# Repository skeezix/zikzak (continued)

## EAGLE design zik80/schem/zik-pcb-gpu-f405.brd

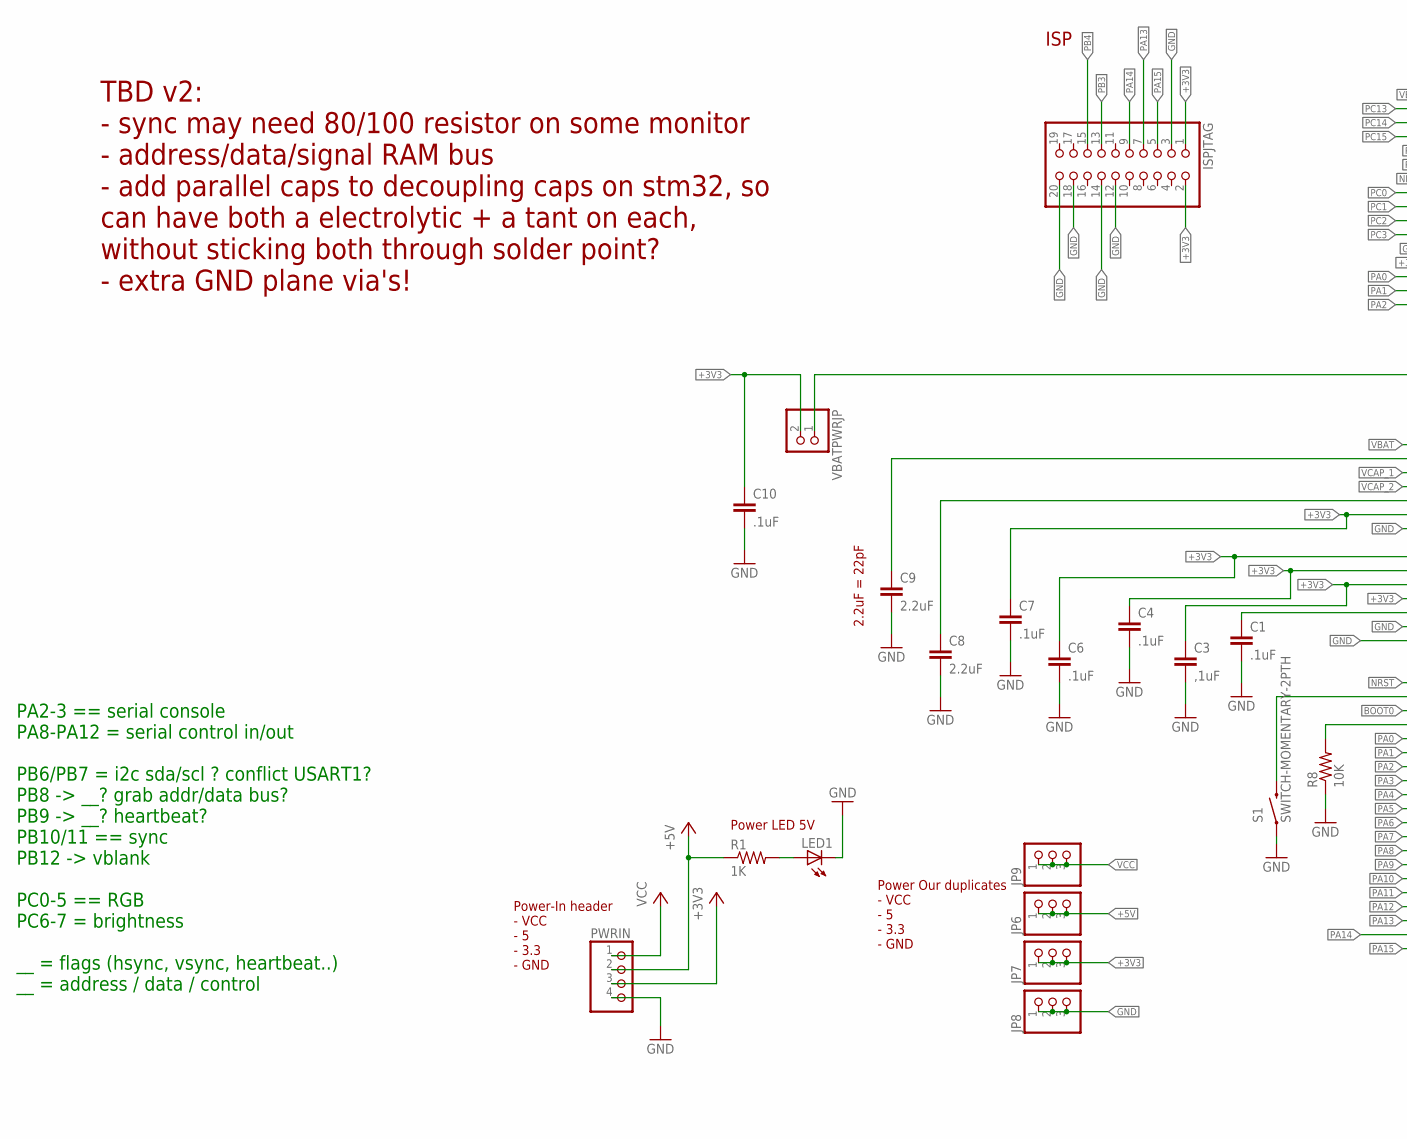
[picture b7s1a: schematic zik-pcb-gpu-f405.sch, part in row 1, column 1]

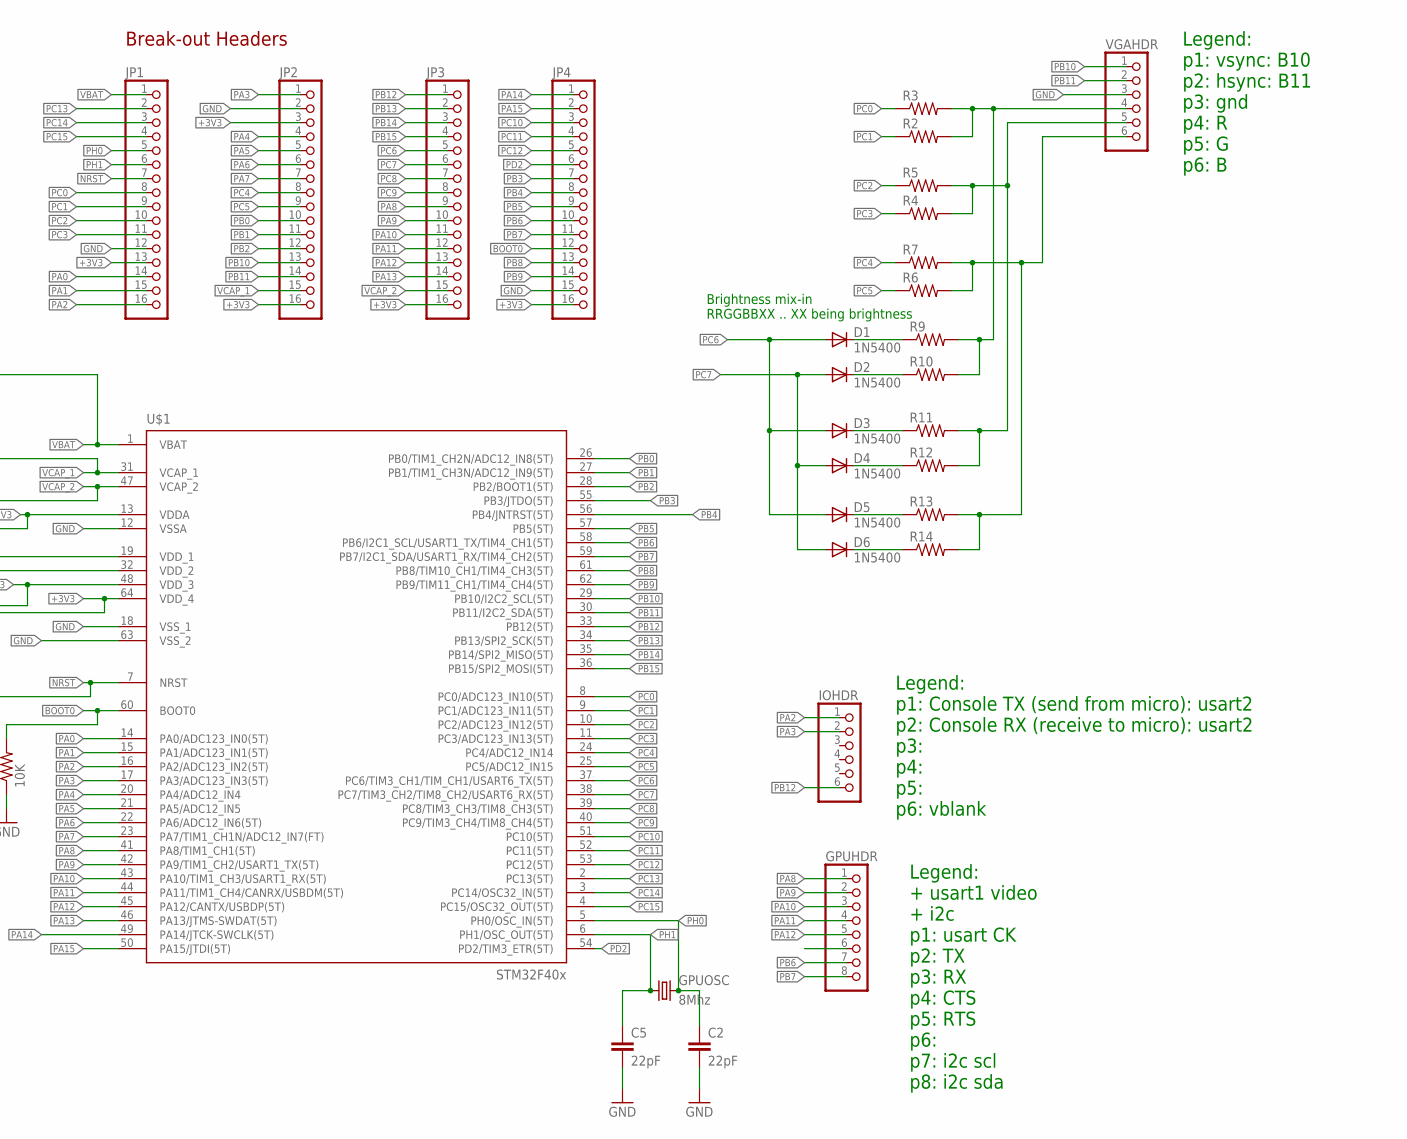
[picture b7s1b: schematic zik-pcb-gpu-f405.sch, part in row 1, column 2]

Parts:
C1, C4, C6, C7, C10: .1uF; C025-025X050
C2, C5: 22pF; C025-025X050
C3: ,1uF; C025-025X050
C8, C9: 2.2uF; C025-025X050
D1, D2, D3, D4, D5, D6: 1N5400; DO201-15
GPUHDR: PINHD-1X8; 1X08
GPUOSC: 8Mhz; HC49US
IOHDR: PINHD-1X6; 1X06
ISPJTAG: PINHD-2X10; 2X10
JP1, JP2, JP3, JP4: PINHD-1X16; 1X16
JP6, JP7, JP8, JP9: PINHD-1X3; 1X03
LED1: LED5MM
PWRIN: PINHD-1X4; 1X04
R1: 1K; 0207/10
R2, R3, R4, R5, R6, R7, R9, R10, R11, R12, R13, R14: R-US_0207/10; 0207/10
R8: 10K; 0207/10
S1: SWITCH-MOMENTARY-2PTH; TACTILE-PTH
U$1: STM32F405R; TQFP64
VBATPWRJP: PINHD-1X2; 1X02
VGAHDR: PINHD-1X6; 1X06

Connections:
+3V3: C1.1, C3.1, C4.1, C6.1, C7.1, C10.1, ISPJTAG.1, ISPJTAG.2, JP1.13, JP2.3, JP2.16, JP3.16, JP4.16, JP7.1, JP7.2, JP7.3, PWRIN.3, U$1.13 (VDDA), U$1.19 (VDD_1), U$1.32 (VDD_2), U$1.48 (VDD_3), U$1.64 (VDD_4), VBATPWRJP.2
+5V: JP6.1, JP6.2, JP6.3, PWRIN.2, R1.1
BOOT0: JP4.12, R8.2, U$1.60 (BOOT0)
GND: C1.2, C2.2, C3.2, C4.2, C5.2, C6.2, C7.2, C8.2, C9.2, C10.2, ISPJTAG.3, ISPJTAG.12, ISPJTAG.14, ISPJTAG.18, ISPJTAG.20, JP1.12, JP2.2, JP4.15, JP8.1, JP8.2, JP8.3, LED1.K (C), PWRIN.4, R8.1, S1.1, U$1.12 (VSSA), U$1.18 (VSS_1), U$1.63 (VSS_2), VGAHDR.3
unnamed: LED1.A, R1.2
unnamed: D1.C, R9.1
unnamed: R4.2, R5.2, R11.2, R12.2, VGAHDR.5
unnamed: D2.C, R10.1
unnamed: R6.2, R7.2, R13.2, R14.2, VGAHDR.6
unnamed: R2.2, R3.2, R9.2, R10.2, VGAHDR.4
unnamed: D3.C, R11.1
unnamed: D4.C, R12.1
unnamed: D5.C, R13.1
unnamed: D6.C, R14.1
NRST: JP1.7, S1.3 (2), U$1.7 (NRST)
PA0: JP1.14, U$1.14 (PA0/ADC123_IN0(5T))
PA1: JP1.15, U$1.15 (PA1/ADC123_IN1(5T))
PA2: IOHDR.1, JP1.16, U$1.16 (PA2/ADC123_IN2(5T))
PA3: IOHDR.2, JP2.1, U$1.17 (PA3/ADC123_IN3(5T))
PA4: JP2.4, U$1.20 (PA4/ADC12_IN4)
PA5: JP2.5, U$1.21 (PA5/ADC12_IN5)
PA6: JP2.6, U$1.22 (PA6/ADC12_IN6(5T))
PA7: JP2.7, U$1.23 (PA7/TIM1_CH1N/ADC12_IN7(FT))
PA8: GPUHDR.1, JP3.9, U$1.41 (PA8/TIM1_CH1(5T))
PA9: GPUHDR.2, JP3.10, U$1.42 (PA9/TIM1_CH2/USART1_TX(5T))
PA10: GPUHDR.3, JP3.11, U$1.43 (PA10/TIM1_CH3/USART1_RX(5T))
PA11: GPUHDR.4, JP3.12, U$1.44 (PA11/TIM1_CH4/CANRX/USBDM(5T))
PA12: GPUHDR.5, JP3.13, U$1.45 (PA12/CANTX/USBDP(5T))
PA13: ISPJTAG.7, JP3.14, U$1.46 (PA13/JTMS-SWDAT(5T))
PA14: ISPJTAG.9, JP4.1, U$1.49 (PA14/JTCK-SWCLK(5T))
PA15: ISPJTAG.5, JP4.2, U$1.50 (PA15/JTDI(5T))
PB0: JP2.10, U$1.26 (PB0/TIM1_CH2N/ADC12_IN8(5T))
PB1: JP2.11, U$1.27 (PB1/TIM1_CH3N/ADC12_IN9(5T))
PB2: JP2.12, U$1.28 (PB2/BOOT1(5T))
PB3: ISPJTAG.13, JP4.7, U$1.55 (PB3/JTDO(5T))
PB4: ISPJTAG.15, JP4.8, U$1.56 (PB4/JNTRST(5T))
PB5: JP4.9, U$1.57 (PB5(5T))
PB6: GPUHDR.7, JP4.10, U$1.58 (PB6/I2C1_SCL/USART1_TX/TIM4_CH1(5T))
PB7: GPUHDR.8, JP4.11, U$1.59 (PB7/I2C1_SDA/USART1_RX/TIM4_CH2(5T))
PB8: JP4.13, U$1.61 (PB8/TIM10_CH1/TIM4_CH3(5T))
PB9: JP4.14, U$1.62 (PB9/TIM11_CH1/TIM4_CH4(5T))
PB10: JP2.13, U$1.29 (PB10/I2C2_SCL(5T)), VGAHDR.1
PB11: JP2.14, U$1.30 (PB11/I2C2_SDA(5T)), VGAHDR.2
PB12: IOHDR.6, JP3.1, U$1.33 (PB12(5T))
PB13: JP3.2, U$1.34 (PB13/SPI2_SCK(5T))
PB14: JP3.3, U$1.35 (PB14/SPI2_MISO(5T))
PB15: JP3.4, U$1.36 (PB15/SPI2_MOSI(5T))
PC0: JP1.8, R3.1, U$1.8 (PC0/ADC123_IN10(5T))
PC1: JP1.9, R2.1, U$1.9 (PC1/ADC123_IN11(5T))
PC2: JP1.10, R5.1, U$1.10 (PC2/ADC123_IN12(5T))
PC3: JP1.11, R4.1, U$1.11 (PC3/ADC123_IN13(5T))
PC4: JP2.8, R7.1, U$1.24 (PC4/ADC12_IN14)
PC5: JP2.9, R6.1, U$1.25 (PC5/ADC12_IN15)
PC6: D1.A, D3.A, D5.A, JP3.5, U$1.37 (PC6/TIM3_CH1/TIM_CH1/USART6_TX(5T))
PC7: D2.A, D4.A, D6.A, JP3.6, U$1.38 (PC7/TIM3_CH2/TIM8_CH2/USART6_RX(5T))
PC8: JP3.7, U$1.39 (PC8/TIM3_CH3/TIM8_CH3(5T))
PC9: JP3.8, U$1.40 (PC9/TIM3_CH4/TIM8_CH4(5T))
PC10: JP4.3, U$1.51 (PC10(5T))
PC11: JP4.4, U$1.52 (PC11(5T))
PC12: JP4.5, U$1.53 (PC12(5T))
PC13: JP1.2, U$1.2 (PC13(5T))
PC14: JP1.3, U$1.3 (PC14/OSC32_IN(5T))
PC15: JP1.4, U$1.4 (PC15/OSC32_OUT(5T))
PD2: JP4.6, U$1.54 (PD2/TIM3_ETR(5T))
PH0: C2.1, GPUOSC.2, JP1.5, U$1.5 (PH0/OSC_IN(5T))
PH1: C5.1, GPUOSC.1, JP1.6, U$1.6 (PH1/OSC_OUT(5T))
VBAT: JP1.1, U$1.1 (VBAT), VBATPWRJP.1
VCAP_1: C9.1, JP2.15, U$1.31 (VCAP_1)
VCAP_2: C8.1, JP3.15, U$1.47 (VCAP_2)
VCC: JP9.1, JP9.2, JP9.3, PWRIN.1

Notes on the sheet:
Power-In header - VCC - 5 - 3.3 - GND
Break-out Headers
ISP
Power Our duplicates - VCC - 5 - 3.3 - GND
2.2uF = 22pF
TBD v2: - sync may need 80/100 resistor on some monitor - address/data/signal RAM bus - add parallel caps to decoupling caps on stm32, so can have both a electrolytic + a tant on each, without sticking both through solder point? - extra GND plane via's!
Power LED 5V
Legend: p1: vsync: B10 p2: hsync: B11 p3: gnd p4: R p5: G p6: B
PA2-3 == serial console PA8-PA12 = serial control in/out PB6/PB7 = i2c sda/scl ? conflict USART1? PB8 -> __? grab addr/data bus? PB9 -> __? heartbeat? PB10/11 == sync PB12 -> vblank PC0-5 == RGB PC6-7 = brightness __ = flags (hsync, vsync, heartbeat..) __ = address / data / control
Legend: p1: Console TX (send from micro): usart2 p2: Console RX (receive to micro): usart2 p3: p4: p5: p6: vblank
Legend: + usart1 video + i2c p1: usart CK p2: TX p3: RX p4: CTS p5: RTS p6: p7: i2c scl p8: i2c sda
Brightness mix-in RRGGBBXX .. XX being brightness

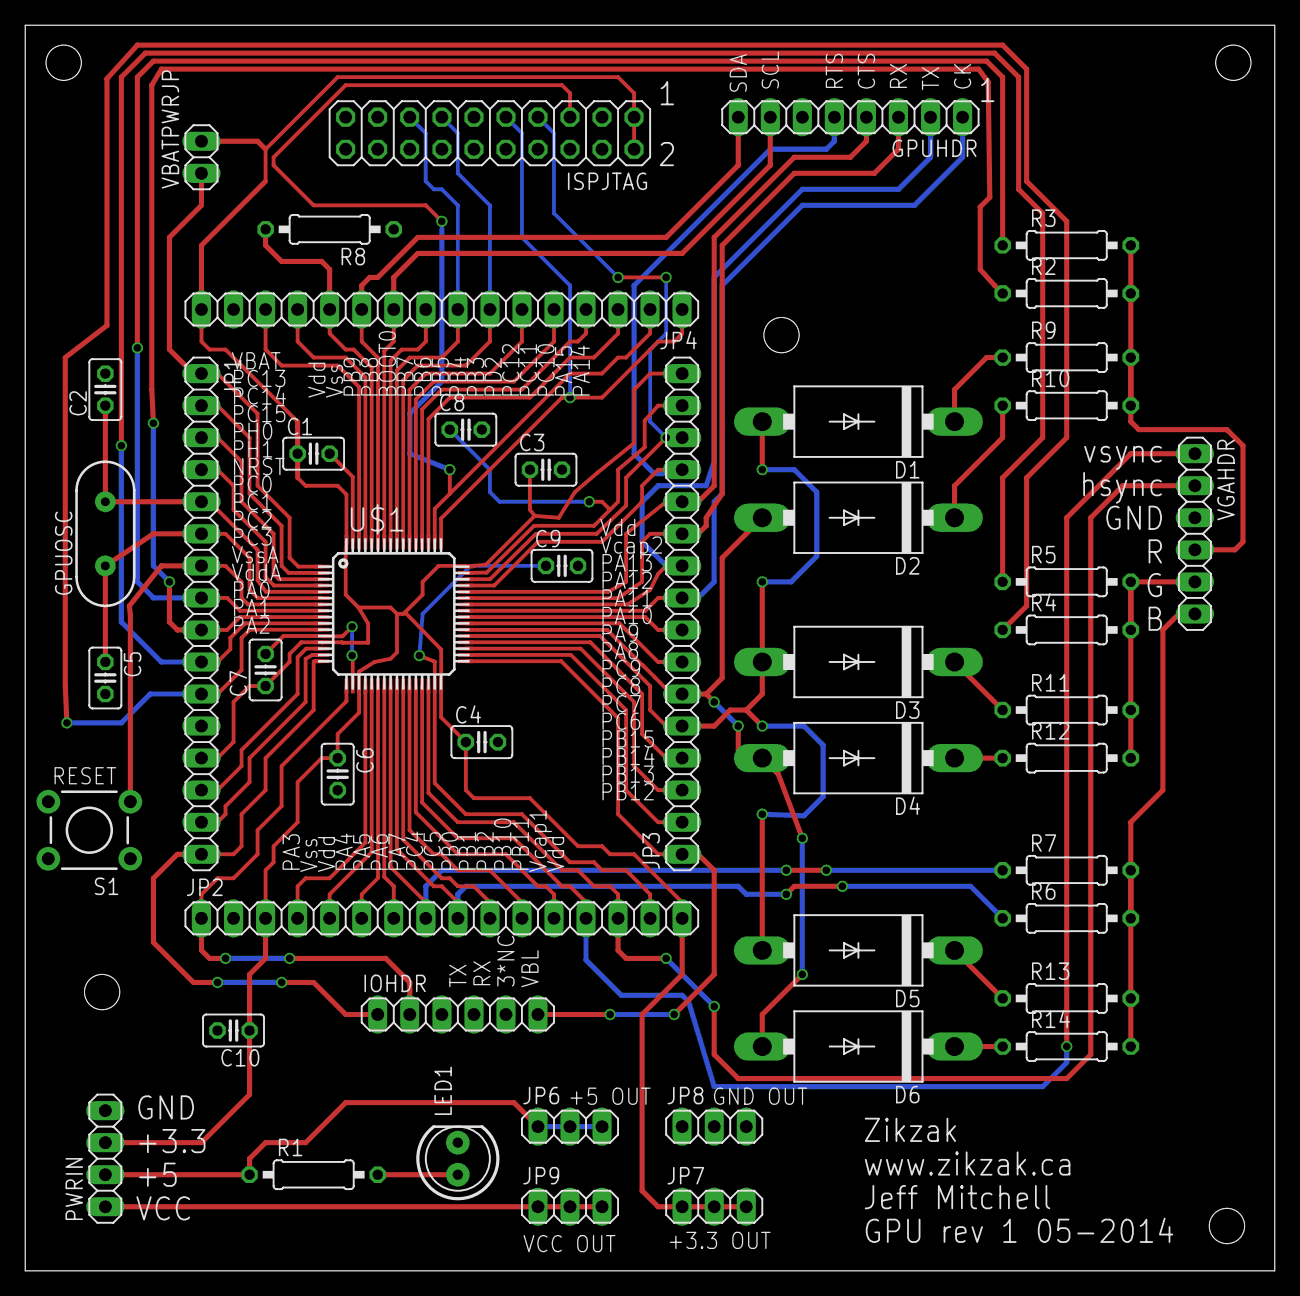
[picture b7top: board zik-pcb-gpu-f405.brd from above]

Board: 2 copper layers, 99.0 x 98.7 mm, 48 parts (0 on the bottom side), 70 nets.

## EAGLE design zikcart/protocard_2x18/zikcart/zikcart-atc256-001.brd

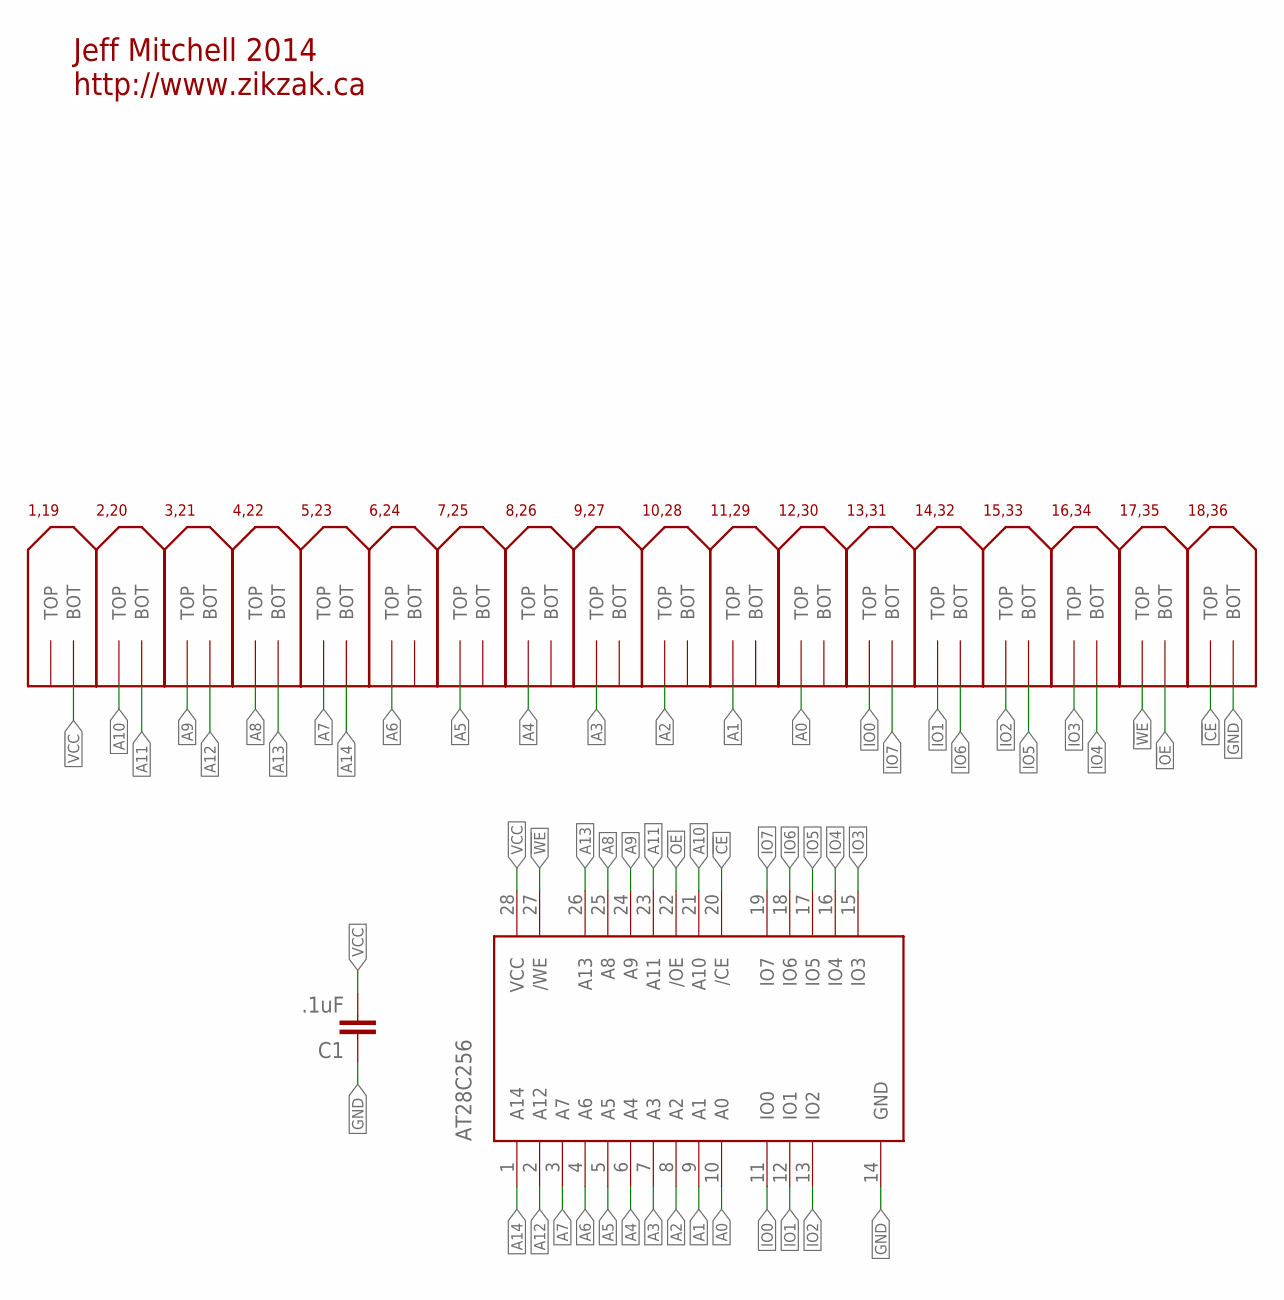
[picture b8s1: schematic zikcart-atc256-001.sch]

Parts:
1,19, 2,20, 3,21, 4,22, 5,23, 6,24, 7,25, 8,26, 9,27, 10,28, 11,29, 12,30, 13,31, 14,32, 15,33, 16,34, 17,35, 18,36: ZIKZAKFINGERPAIR2X18
AT28C256: AT28C256; DIL28-6
C1: .1uF; C025-030X050

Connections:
!CE!: 18,36.P$1 (TOP), AT28C256.20 (/CE)
!OE!: 17,35.P$2 (BOT), AT28C256.22 (/OE)
!WE!: 17,35.P$1 (TOP), AT28C256.27 (/WE)
A0: 12,30.P$1 (TOP), AT28C256.10 (A0)
A1: 11,29.P$1 (TOP), AT28C256.9 (A1)
A2: 10,28.P$1 (TOP), AT28C256.8 (A2)
A3: 9,27.P$1 (TOP), AT28C256.7 (A3)
A4: 8,26.P$1 (TOP), AT28C256.6 (A4)
A5: 7,25.P$1 (TOP), AT28C256.5 (A5)
A6: 6,24.P$1 (TOP), AT28C256.4 (A6)
A7: 5,23.P$1 (TOP), AT28C256.3 (A7)
A8: 4,22.P$1 (TOP), AT28C256.25 (A8)
A9: 3,21.P$1 (TOP), AT28C256.24 (A9)
A10: 2,20.P$1 (TOP), AT28C256.21 (A10)
A11: 2,20.P$2 (BOT), AT28C256.23 (A11)
A12: 3,21.P$2 (BOT), AT28C256.2 (A12)
A13: 4,22.P$2 (BOT), AT28C256.26 (A13)
A14: 5,23.P$2 (BOT), AT28C256.1 (A14)
GND: 18,36.P$2 (BOT), AT28C256.14 (GND), C1.1
IO0: 13,31.P$1 (TOP), AT28C256.11 (IO0)
IO1: 14,32.P$1 (TOP), AT28C256.12 (IO1)
IO2: 15,33.P$1 (TOP), AT28C256.13 (IO2)
IO3: 16,34.P$1 (TOP), AT28C256.15 (IO3)
IO4: 16,34.P$2 (BOT), AT28C256.16 (IO4)
IO5: 15,33.P$2 (BOT), AT28C256.17 (IO5)
IO6: 14,32.P$2 (BOT), AT28C256.18 (IO6)
IO7: 13,31.P$2 (BOT), AT28C256.19 (IO7)
VCC: 1,19.P$2 (BOT), AT28C256.28 (VCC), C1.2

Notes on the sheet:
Jeff Mitchell 2014 http://www.zikzak.ca

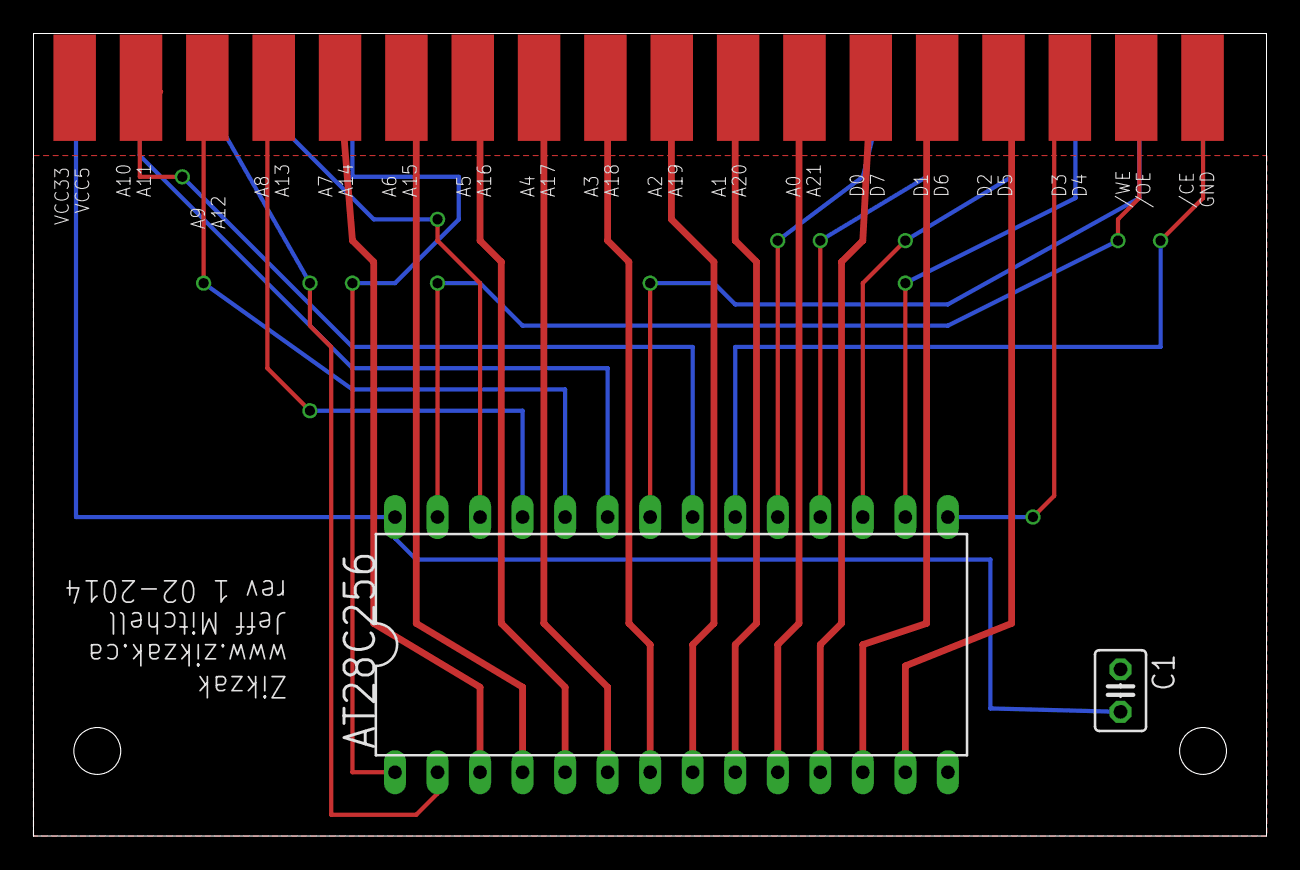
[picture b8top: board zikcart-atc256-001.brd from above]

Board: 2 copper layers, 73.6 x 47.9 mm, 20 parts (0 on the bottom side), 28 nets.

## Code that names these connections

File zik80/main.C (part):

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  OCR0B = 0;
  
  // Timer 1 - vertical sync pulses
  DDRD |= (1<<PD4); // vsync
  Timer1::setMode (15, Timer1::PRESCALE_1024, Timer1::CLEAR_B_ON_COMPARE);
  OCR1A = 259;  // 16666 / 64 uS = 260 (less one)
  OCR1B = 0;    // 64 / 64 uS = 1 (less one)
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  TIMSK1 = bit (TOIE1);  // interrupt on overflow on timer 1

  // Timer 2 - horizontal sync pulses
  DDRD |= (1<<PD6); // hsync
  Timer2::setMode (7, Timer2::PRESCALE_8, Timer2::CLEAR_B_ON_COMPARE);
  OCR2A = 63;   // 32 / 0.5 uS = 64 (less one)
  OCR2B = 7;    // 4 / 0.5 uS = 8 (less one)
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  // baud rate must be zero before enabling the transmitter
  UBRR0 = 0;  // USART Baud Rate Register
  //pinMode (MSPIM_SCK, OUTPUT);   // set XCK pin as output to enable master mode
  DDRB |= (1<<PB0);
  UCSR0B = 0; 
  UCSR0C = bit (UMSEL00) | bit (UMSEL01) | bit (UCPHA0) | bit (UCPOL0);  // Master SPI mode

  // prepare to sleep between horizontal sync pulses  
  set_sleep_mode ( SLEEP_MODE_IDLE );  

  DDRD |= (1<<PD0); // red
  DDRD |= (1<<PD1); // green
  DDRD |= (1<<PD2); // blue

  // JOY: set up pin change interupts
  EICRA &= ~ ( (1 << ISC11) | (1 << ISC10) ); // reset: clear ISC11+ISC10 (ISC1x for vect1 which we need for joy)
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}  // end of loop

volatile unsigned char _g_joy_state = 0; // so we can know which pins changed since last interupt
#define JOYMASK ( (1<<PB2) | (1<<PB3) | (1<<PB4) | (1<<PB5) | (1<<PB6) )
ISR(PCINT1_vect)
{
  unsigned char delta = _g_joy_state ^ PINB;

  if ( delta & (1<<PB2) ) {

    // CH1: edge has gone up, or down?
    if ( PINB & ( 1 << PB2 ) ) {
      // JOY UP: edge has gone high (nolonger pointing up)
      textbuf [ 0 ][ 0 ] = ' ';

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
  textbuf [ 0 ][ 4 ] = 'C';

  if ( PINC & ( 1 << PC5 ) ) {
    textbuf [ 0 ][ 2 ] = 'K';
  }

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
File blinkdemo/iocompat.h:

/*
 * ----------------------------------------------------------------------------
 * "THE BEER-WARE LICENSE" (Revision 42):
 * <joerg@FreeBSD.ORG> wrote this file.  As long as you retain this notice you
 * can do whatever you want with this stuff. If we meet some day, and you think
 * this stuff is worth it, you can buy me a beer in return.        Joerg Wunsch
 * ----------------------------------------------------------------------------
 *
 * IO feature compatibility definitions for various AVRs.
 *
 * $Id: iocompat.h 1638 2008-03-17 21:52:00Z joerg_wunsch $
 */

#if !defined(IOCOMPAT_H)
#define IOCOMPAT_H 1

/*
 * Device-specific adjustments:
 *
 * Supply definitions for the location of the OCR1[A] port/pin, the
 * name of the OCR register controlling the PWM, and adjust interrupt
 * vector names that differ from the one used in demo.c
 * [TIMER1_OVF_vect].
 */
#if defined(__AVR_AT90S2313__)
#  define OC1 PB3
#  define OCR OCR1
#  define DDROC DDRB
#  define TIMER1_OVF_vect TIMER1_OVF1_vect
#elif defined(__AVR_AT90S2333__) || defined(__AVR_AT90S4433__)
#  define OC1 PB1
#  define DDROC DDRB
#  define OCR OCR1
#elif defined(__AVR_AT90S4414__) || defined(__AVR_AT90S8515__) || \
      defined(__AVR_AT90S4434__) || defined(__AVR_AT90S8535__) || \
      defined(__AVR_ATmega163__) || defined(__AVR_ATmega8515__) || \
      defined(__AVR_ATmega8535__) || \
      defined(__AVR_ATmega164P__) || defined(__AVR_ATmega324P__) || \
      defined(__AVR_ATmega644__) || defined(__AVR_ATmega644P__) || \
      defined(__AVR_ATmega1284P__)
#  define OC1 PD5
#  define DDROC DDRD
#  define OCR OCR1A
#  if !defined(TIMSK)		/* new ATmegas */
#    define TIMSK TIMSK1
#  endif
#elif defined(__AVR_ATmega8__) || defined(__AVR_ATmega48__) || \
      defined(__AVR_ATmega88__) || defined(__AVR_ATmega168__)
#  define OC1 PB1
#  define DDROC DDRB
#  define OCR OCR1A
#  if !defined(TIMSK)		/* ATmega48/88/168 */
#    define TIMSK TIMSK1
#  endif /* !defined(TIMSK) */
#elif defined(__AVR_ATtiny2313__)
#  define OC1 PB3
#  define OCR OCR1A
#  define DDROC DDRB
#elif defined(__AVR_ATtiny24__) || defined(__AVR_ATtiny44__) || \
      defined(__AVR_ATtiny84__)
#  define OC1 PA6
#  define DDROC DDRA
#  if !defined(OCR1A)
#    /* work around misspelled name in avr-libc 1.4.[0..1] */
#    define OCR OCRA1
#  else
#    define OCR OCR1A
#  endif
#  define TIMSK TIMSK1
#  define TIMER1_OVF_vect TIM1_OVF_vect /* XML and datasheet mismatch */
#elif defined(__AVR_ATtiny25__) || defined(__AVR_ATtiny45__) || \
      defined(__AVR_ATtiny85__)
/* Timer 1 is only an 8-bit timer on these devices. */
#  define OC1 PB1
#  define DDROC DDRB
#  define OCR OCR1A
#  define TCCR1A TCCR1
#  define TCCR1B TCCR1
#  define TIMER1_OVF_vect TIM1_OVF_vect
#  define TIMER1_TOP 255	/* only 8-bit PWM possible */
#  define TIMER1_PWM_INIT _BV(PWM1A) | _BV(COM1A1)
#  define TIMER1_CLOCKSOURCE _BV(CS12) /* use 1/8 prescaler */
#elif defined(__AVR_ATtiny26__)
/* Rather close to ATtinyX5 but different enough for its own section. */
#  define OC1 PB1
#  define DDROC DDRB
#  define OCR OCR1A
#  define TIMER1_OVF_vect TIMER1_OVF1_vect
#  define TIMER1_TOP 255	/* only 8-bit PWM possible */
#  define TIMER1_PWM_INIT _BV(PWM1A) | _BV(COM1A1)
#  define TIMER1_CLOCKSOURCE _BV(CS12) /* use 1/8 prescaler */
/*
 * Without setting OCR1C to TOP, the ATtiny26 does not trigger an
 * overflow interrupt in PWM mode.
 */
#  define TIMER1_SETUP_HOOK() OCR1C = 255
#elif defined(__AVR_ATtiny261__) || defined(__AVR_ATtiny461__) || \
      defined(__AVR_ATtiny861__)
#  define OC1 PB1
#  define DDROC DDRB
#  define OCR OCR1A
#  define TIMER1_PWM_INIT _BV(WGM10) | _BV(PWM1A) | _BV(COM1A1)
/*
 * While timer 1 could be operated in 10-bit mode on these devices,
 * the handling of the 10-bit IO registers is more complicated than
 * that of the 16-bit registers of other AVR devices (no combined
 * 16-bit IO operations possible), so we restrict this demo to 8-bit
 * mode which is pretty standard.
 */
#  define TIMER1_TOP 255
#  define TIMER1_CLOCKSOURCE _BV(CS12) /* use 1/8 prescaler */
#elif defined(__AVR_ATmega32__) || defined(__AVR_ATmega16__)
#  define OC1 PD5
#  define DDROC DDRD
#  define OCR OCR1A
#elif defined(__AVR_ATmega64__) || defined(__AVR_ATmega128__) || \
      defined(__AVR_ATmega165__) || defined(__AVR_ATmega169__) || \
      defined(__AVR_ATmega325__) || defined(__AVR_ATmega3250__) || \
      defined(__AVR_ATmega645__) || defined(__AVR_ATmega6450__) || \
      defined(__AVR_ATmega329__) || defined(__AVR_ATmega3290__) || \
      defined(__AVR_ATmega649__) || defined(__AVR_ATmega6490__) || \
      defined(__AVR_ATmega640__) || \
      defined(__AVR_ATmega1280__) || defined(__AVR_ATmega1281__) || \
      defined(__AVR_ATmega2560__) || defined(__AVR_ATmega2561__)
#  define OC1 PB5
#  define DDROC DDRB
#  define OCR OCR1A
#  if !defined(PB5) 		/* work around missing bit definition */
#    define PB5 5
#  endif
#  if !defined(TIMSK)		/* new ATmegas */
#    define TIMSK TIMSK1
#  endif
#else
#  error "Don't know what kind of MCU you are compiling for"
#endif

/*
 * Map register names for older AVRs here.
 */
#if !defined(COM1A1)
#  define COM1A1 COM11
#endif

#if !defined(WGM10)
#  define WGM10 PWM10
#  define WGM11 PWM11
#endif

/*
 * Provide defaults for device-specific macros unless overridden
 * above.
 */
#if !defined(TIMER1_TOP)
#  define TIMER1_TOP 1023	/* 10-bit PWM */
#endif

#if !defined(TIMER1_PWM_INIT)
#  define TIMER1_PWM_INIT _BV(WGM10) | _BV(WGM11) | _BV(COM1A1)
#endif

#if !defined(TIMER1_CLOCKSOURCE)
#  define TIMER1_CLOCKSOURCE _BV(CS10) /* full clock */
#endif

#endif /* !defined(IOCOMPAT_H) */

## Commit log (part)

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2013-05-02 Initial
2013-05-06 setting git remote up
2013-05-07 Added blinkdemo and lcdtest and some junk
2013-05-07 bitches be crazy
2013-05-11 messing around
2013-05-11 cleaning up
2013-05-11 nearly working line-based VGA demo :)
2013-05-13 scribble update
2013-05-15 updating sram test.. still not working :(
2013-05-17 first cut of inventory
2013-05-18 inventory update
2013-05-25 added preliminary inkscape drawing of memory switcher
2013-05-26 added lazarus-64 pics in case I need them
2013-05-28 Inventory update, and preliminary memswitcher schematic (address lines are in)
2013-05-29 Inventory; fiddled with blinkdemo to convert to atmega128
2013-05-29 updated notes on 64/40 cpu/gpu
2013-05-30 schematic update
2013-05-31 updated schematic
2013-06-01 inventory update (used parts up), added a gpu blinker
2013-06-05 Some new code for cpu and gpu, clarified schematic
2013-06-06 fiddling; put in nice ram module
2013-06-06 added photos
2013-06-11 inventory; added d type flipflops, among others
2013-06-11 stable random colour per scanline, dual buffering.. works!
2013-06-28 Split off gpu onto its own board..
2013-08-03 Updating inventory
2013-08-13 removed inventory from git, so can publish publicly
2013-10-18 Kicked off zikzak-z80 schematic
2013-10-22 Added resistor values to zz r3 schem
2013-10-23 Instead of my own text dump variant, using this version which steals a lot from Nick Gammon; works better due to interupt driving. Funny how interupts were too latent for my earlier experiments; that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
2013-10-23 Added basic wiring notes for future reference
2013-11-03 note about long term storage
2013-11-04 oops
2013-11-04 Fix, changed a 5v->GND on a LED
2013-11-06 basic joystick sensing.. works! corrections to schematic (pull up, not down, on joystick.)
2013-11-06 first cut at capturing keyboard clock interupt
2013-11-15 Update to add IO mcu to zik80 design
2013-11-15 Updated schem
2013-11-19 breadboard: added joy port; joy-up raises/lowers the IO LED as appropriate, woowoo
2013-11-20 moving schems to more convenient location, for r5 design WIP
2013-11-20 Slightly better naming of globals in keyb lib
2014-01-06 first setup of audio experiment, atmega644 driving ay-3-8910 (8912 in this case); same as ST YM2149 :) .. just LED blinker so far, and hookup notes .. BB is hooked up!
2014-01-07 AY-3-8912 audio is playing just-fine from avr to audio chip :)
2014-01-07 Fiddling around with pulling .ym bits in
2014-01-08 added YM-file conversion to play simple Atari ST (etc) songs/demos
2014-01-15 stm32: working interupt based blinker; some nasty lessons learnt, and now trying to work out how fast we can do these in reality.
2014-01-15 vsync timing looks more or less correct, so time to put in the line content drawing, the hsync, add the port and DAC back to breadboard and see whaaaas happenin'!
2014-01-16 Basic VGA is working; a little shakey, need to tweak timings, etc etc, buy hey.. it does _Something_, which is not bad for a couple hours.
2014-01-17 Perfectly sharp vga to the composite adaptor; no wiggles or distortion, RGB supported. Approx 120*600 resolution, and not using DMA yet.
2014-01-17 unrolled the loop, and with RGB array reading, in straight bloring non-DMA c, we're getting about 180x600 :)
2014-01-19 Thrashing around trying to get dma to gpio working..
2014-01-19 DMA screwing around.. seems like it never finishes.. never starts? even in the provided CMSIS sample :/
2014-01-19 DMA based VGA is working very nicely.. full colour at 320x200 up to 600x600 and more .. aweesome!
2014-01-20 DMA working pretty well; trying on real monitor.. too much jitter when pixels change colour .. hmm.. need SPI maybe?
2014-01-23 Set to 168MHz.. woowoo :)
2014-01-23 Found some nifty code in a youtube video; pulled it in, can take a look later; he's doing the clocks on sync like I'm working on, so can crib his timings :O
2014-01-26 Skeleton update.. F4 vga
2014-01-27 Was screwiung around with pulling in code from doodles stuff (see _reference) but it is not something you can do quickly to get some timing info from; it is too comprehensive. So I think, back to my 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
2014-01-27 Fiddling with DMA setup
2014-01-30 VGA is working solid! stm32-f4-vga dir; sharp, no jiggle, bullet proof!
2014-01-30 Some examples from stm32 forum; being stuck on timing, I was bugging clive et al for assistance
2014-01-30 alight anim improvement; worry: doing too much during 'vblank' borks up the top few lines of the display; am I cpu locked here? shouldn't interupts take over from main painlessly without sync issues?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
2014-01-31 vga fiddling; some slight lame optims, and performance testing; memcpy bad apparently .. but why is main busy loop impacting ISRs so much? still, not too shabby
2014-01-31 Disable the dma deinit/cmd before dma setup, since its already finished if we're doing our jobs right; some minor optimization in the pixel pushing, so we can go faster.. not fast enough yet, but not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
2014-02-01 Added basic 'torture'; turns up a timer, hits 100 times a sec, and shows some flicker on display :/
2014-02-01 okay, interupt itself is okay; if gpio reads/writes are during vblank is okay; but if int goes off and read gpio, during non-vblank, it'll turd a bit. if interupt occurs and set volatile, and then an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
2014-02-02 For lulz, added a (commented out) dma-from-SRAM2 option, and gltching still occurs; the problem is twofols .. hitting SRAM1 during DMA, or hitting GPIO during DMA, will glitch. Use FSMC memory contro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
2014-02-03 VGA fiddling more .. slightly optimize non-DMA approach, so its pretty workable; less glitchign when GPIOs going on, so maybe workable without intermediary; still lots of avenues to pursue that may a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
2014-02-08 Added basic bitbang server to stm32f4 GPU; added contained avr8 code to push sprite-move requests to stm32 f4, for timing testing, at 8MHz avr8. Not too bad. Little shakey on the protocol due to hsyn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
2014-02-22 Adding some parts sources
2014-02-27 zikcart schem at28c256 18x2 is in good shape; just started pcb layout however
2014-02-28 First board submission to elecrow! (on special, 50% off small boards)
2014-03-03 Running arm code from buffer experiments
2014-03-08 Received rev1 zikcart pcb; added pics
2014-03-10 Added a zikcart pic
2014-04-26 Just starting the new zikzak base board; 5V and 3.3V power supply nearly done.. need to add Vcc Vss Posts and DC jack
2014-05-05 import eagle libs; update base schematic
2014-05-10 Renaming zik base schem, to pcb-power .. and added pcb-gpu. Going to mnake more little pcbs instead of one biggy, for this stage.. combine them later
2014-05-10 Updating schem for gpu
2014-05-21 Basic gpu pcb schem is done! Need to verify, and route, and good to go?
2014-05-23 few mods to the power pcb schem; finalizing the gpu pcb schem; started power pcb board layout.. woowoo!
2014-05-24 rev1 of both power and gpu boards finalized, and elecrow gerber files generated!
2014-06-04 Made a couple notes on power and gpu schems, of things needing correction; fiddled with vga out on real pcb.. works!
2014-06-04 commiting missing bits
2014-06-05 Started fiddling with serial server and serial client (stm32, atmega644, respectively)
2014-06-07 Got usart2 serial demo working; stupid typo. now to get avr serial proven to desktop again, then hook up the avr to gpio serial header, and awwwway we go!
2014-06-09 Added skeleton for serial+VGA; vga working nice, put together 640x480x60hz timings with 2* 256x192 framebuffers; serial is screwy due to clock change, need to sort it
2014-06-11 Image with 1px-wide colours is now solid; DMA is now render option again; serial logging doesn't impact render now; great foundation for working on animation
2014-06-11 Basic serial server works.. can type in clear, fill, linedraws, or send them from a simple program
2014-06-11 Forgot to include new config file
2014-06-12 cosmetics
2014-06-19 Added preliminary lame colour-space downconverter for images .. convert RGB888 to RRGGBBXX :) Works alright!
2014-06-20 Initial kickoff of zik80 base pcb
2014-06-24 base pcb with built in ez80 is more or less ready; time to make pcb..
2014-06-26 Working on base pcb .. nearly there, but last few traces will take hours..
2014-06-28 zikzak base pcb rev1 sent to boardhouse :)
2014-07-05 minor fiddling; new photos of gpu rev2 + base rev1, and tweak to serial-bug-vga on f429 (due to debug serial -> vga glitch)
2014-07-07 schem image for base pcb added rev1
2014-07-10 photo: zikbase with zikcart
2014-07-11 Basic test code for audio, gpio, etc .. so far so good!
2014-07-17 Added pics
2014-07-18 Fiddling for fun .. added basic linedraw demo to the z80 code
2014-07-26 working on first cut of new pcb layout
2014-08-16 Working on SBC (single board computer) version of zik80; solid schem, very earily pcb layout; oddly enough, an auto-route does a pretty good job, so.. tempting .. but naah :)
2014-08-18 Trundling along.
2014-08-29 zik80 sbc pcb arrived and mostly populated.. photos added, testing commencing
2014-08-30 Photo of bad solder glitch, trying to debug..
2014-09-04 zik80 sbc .. more fiddling; lame on screen menu, serial keyboard control; still too slow .. need to use scenegraph approach :/
2014-09-06 Basic sprite demo on gpu side; essentially simulating preliminary sprite capability when pulling tilemap from ram, with overlaid sprites
2014-10-17 ehh, intermediate temp file screwerey
2014-11-06 schem exported image
2014-11-22 Final(?) rev3 zikzak sbc; created brand new zok atmega644 BoB design and board, WIP
2014-11-25 Packaged up the files for elecrow ..
2014-12-05 zikzak sbc rev3 basic testing.. audio good! 512KB RAM good! time to get serious..
2014-12-09 Basic gpu textmode+sprite-list going, basic HAL header created
2014-12-09 Basic HAL and BIOS code in place; rudimentary textmode+sprite demo built in
2014-12-10 image of schem, new photo
2014-12-10 Resized
2015-04-07 stm-f4-sensors may not work (or maybe board is flaky for serial, or serial usb adapter...)
2015-10-29 Flailing around with eZ80 interupts and ps/2 keyboard handler; why the hell is it not working?
2015-10-30 PS/2 keyboard interupt code is working! Goddamn that was annoying to debug...
2015-10-30 ps/2 protocol and keyboard fiddling (show scancodes), and audio (some standard tones and farty noises)
2015-11-02 Text description changes to zikzak SBC rev3 pcb schematic, for clarification on component values etc. No pcb actual changes or schem changes.
2015-11-02 minor change
2015-11-04 branched from r3 to r4 zikzak sbc .. added mixer and audio amp/volume circuit
2015-11-04 adding a audio circuit schem image
2015-11-06 Fiddling with YM file playback from cart/program
2016-05-03 Added basic -shield schem, as I work on the library parts creation
2016-05-03 Ended up modding a lib
2016-05-03 Tweaking skeezix library for ZZ connectors
2016-05-03 Fixing..
2016-05-03 Tweaking library some more
2016-05-09 Updated headphone part
2016-05-12 Added basic avr FTDI/serial tester (for zok board)
2016-05-12 Dropped TPS7133QP and FTDI onto shield start
2016-05-14 shield - Some placement progress
2016-05-15 Shield pcb rough layout coming together nicely
2016-05-15 Shield incremental
2016-05-16 Shield schem nearly final, just need to lay down traces on pcb
2016-05-16 Exported images of stuff
2016-05-16 Shield Routing..
2016-05-17 Shield is routed and checked... ready for boardhouse!
2016-05-26 Testing zikshield r1 on zzr3 .. so far so good ps/2 keyb, usb power/serial, VGA jacks; beautiful :)
2016-05-27 Started working on case desig for 3d printing
2016-05-27 Exported STLs in mini-format
2016-05-29 Added new 2U type case, nearly done, out of batteries :)
2016-05-31 quickie photo of case top
2016-06-03 For ZZ ez80 firmware, got project settings sorted so can Debug (to RAM) or Release (to flash) on the ZZ board; save on those precious few writes, and also a faster turnaround cycle for testing.. winw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
2018-07-18 Update ym-file-format.txt
    Corrected a mistake in the sample number declaration (WORD, not DWORD), added a note about the R3 when using digidrums (an (undocumented?) bit is missing).
